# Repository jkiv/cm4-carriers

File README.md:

# cm4-carriers

## About

This repository contains various Raspberry Pi Compute Module 4 (CM4) carrier boards designed with specific applications in mind.

It also contains "template" boards from which application-specific boards can be quickly derived.

## Boards

### `hardware/cm4-carrier-template`

#### About
A 90mm x 90mm carrier board that can be used as a basis for application-specific boards.

This board can also be used to program the eMMC memory for use on other carrier boards.

#### Features
* Independent power and data USB 2.0 connectors (Type-C)

### `hardware/cm4-carrier-net`

#### About
A 40mm x 90mm carrier board that provides the CM4 with a Gigabit Ethernet interface.

This board can also be used to program the eMMC memory for use on other carrier boards.

#### Features
* Gigabit Ethernet
* USB 2.0 shared power and data connector (Type-C)
* Micro SD card slot

## Donate

Please consider supporting this project and others like it by donating:

* ☕: [ko-fi.com/jkiv_](https://ko-fi.com/jkiv_)
* ₿: `13zRrs1YDdooUN5WtfXRSDn8KnJdok4qG9`

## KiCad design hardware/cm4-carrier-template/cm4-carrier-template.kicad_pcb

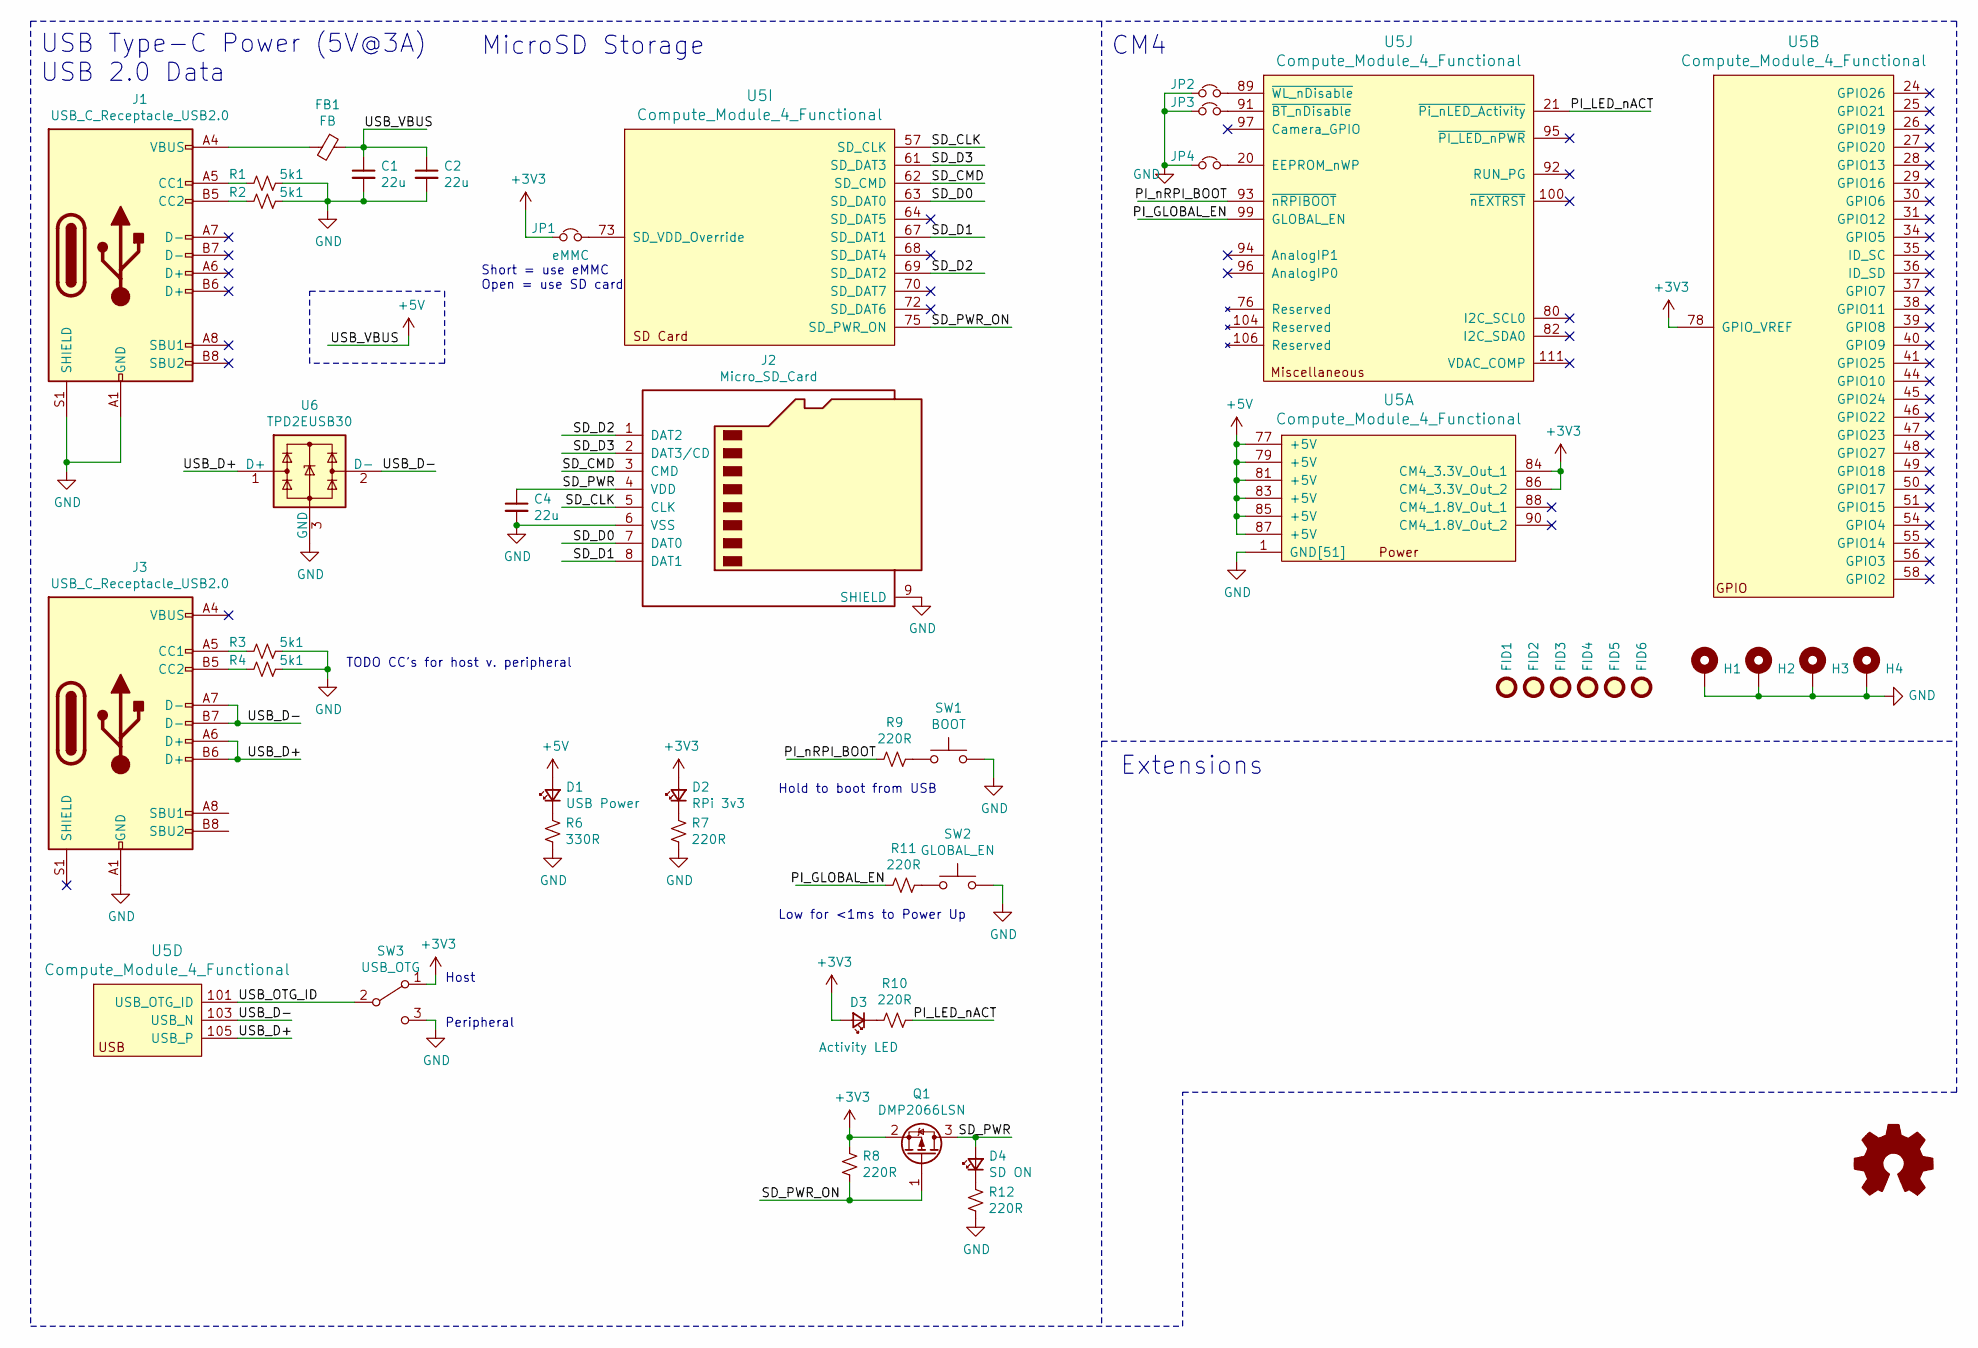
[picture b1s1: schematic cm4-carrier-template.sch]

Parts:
C1, C2, C4: 22u; C_0805_2012Metric
D1: USB Power; LED_0603_1608Metric
D2: RPi 3v3; LED_0603_1608Metric
D3: Activity LED; LED_0603_1608Metric
D4: SD ON; LED_0603_1608Metric
FB1: FB; L_0805_2012Metric
FID1, FID2, FID3, FID4, FID5, FID6: Fiducial; Fiducial_0.75mm_Mask1.5mm
H1, H2, H3, H4: MountingHole_Pad; MountingHole_2.7mm_M2.5_Pad_Via
J1, J3: USB_C_Receptacle_USB2.0; USB_C_Receptacle_GCT-USB4105
J2: Micro_SD_Card; microSD_HC_Molex_104031-0811
JP1: eMMC; J_Small_NC
JP2: ~WL_nDisable; J_Small_NC
JP3: ~BT_nDisable; J_Small_NC
JP4: EEPROM_nWP; J_Small_NC
LOGO1: Logo_Open_Hardware_Small; OSHW-Symbol_6.7x6mm_Copper
Q1: DMP2066LSN; SC-59
R1, R2, R3, R4: 5k1; R_0603_1608Metric
R6: 330R; R_0603_1608Metric
R7, R8, R9, R10, R11, R12: 220R; R_0603_1608Metric
SW1: BOOT; SW_SPST_B3U-1000P
SW2: GLOBAL_EN; SW_SPST_B3U-1000P
SW3: USB_OTG; SW_SPDT_CK-JS102011SAQN
U5: Compute_Module_4_Functional; Raspberry-Pi-4-Compute-Module
U6: TPD2EUSB30; Texas_DRT-3

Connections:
+3V3: D2.2 (A), D3.2 (A), JP1.1, Q1.2 (S), R8.2, SW3.1 (A), U5.78 (GPIO_VREF), U5.84 (CM4_3.3V_Out_1), U5.86 (CM4_3.3V_Out_2)
+5V: C1.1, C2.1, D1.2 (A), FB1.1, U5.77 (+5V), U5.79 (+5V), U5.81 (+5V), U5.83 (+5V), U5.85 (+5V), U5.87 (+5V)
/PI_GLOBAL_EN: R11.2, U5.99 (GLOBAL_EN)
/PI_LED_nACT: R10.1, U5.21 (~Pi_nLED_Activity)
/PI_nRPI_BOOT: R9.2, U5.93 (~nRPIBOOT)
/SD_CLK: J2.5 (CLK), U5.57 (SD_CLK)
/SD_CMD: J2.3 (CMD), U5.62 (SD_CMD)
/SD_D0: J2.7 (DAT0), U5.63 (SD_DAT0)
/SD_D1: J2.8 (DAT1), U5.67 (SD_DAT1)
/SD_D2: J2.1 (DAT2), U5.69 (SD_DAT2)
/SD_D3: J2.2 (DAT3/CD), U5.61 (SD_DAT3)
/SD_PWR: C4.1, D4.2 (A), J2.4 (VDD), Q1.3 (D)
/SD_PWR_ON: Q1.1 (G), R8.1, U5.75 (SD_PWR_ON)
/USB_D+: J3.A6 (D+), J3.B6 (D+), U5.105 (USB_P), U6.1 (D+)
/USB_D-: J3.A7 (D-), J3.B7 (D-), U5.103 (USB_N), U6.2 (D-)
/USB_OTG_ID: SW3.2 (B), U5.101 (USB_OTG_ID)
GND: C1.2, C2.2, C4.2, H1.1, H2.1, H3.1, H4.1, J1.A1 (GND), J1.A12 (GND), J1.B1 (GND), J1.B12 (GND), J1.S1 (SHIELD), J2.6 (VSS), J2.9 (SHIELD), J3.A1 (GND), J3.A12 (GND), J3.B1 (GND), J3.B12 (GND), JP2.1, JP3.1, JP4.1, R1.1, R2.1, R3.1, R4.1, R6.2, R7.2, R12.2, SW1.2, SW2.2, SW3.3 (C), U5.1 (GND[51]), U5.2 (GND[51]), U5.7 (GND[51]), U5.8 (GND[51]), U5.13 (GND[51]), U5.14 (GND[51]), U5.22 (GND[51]), U5.23 (GND[51]), U5.32 (GND[51]), U5.33 (GND[51]), U5.42 (GND[51]), U5.43 (GND[51]), U5.52 (GND[51]), U5.53 (GND[51]), U5.59 (GND[51]), U5.60 (GND[51]), U5.65 (GND[51]), U5.66 (GND[51]), U5.71 (GND[51]), U5.74 (GND[51]), U5.98 (GND[51]), U5.107 (GND[51]), U5.108 (GND[51]), U5.113 (GND[51]), U5.114 (GND[51]), U5.119 (GND[51]), U5.120 (GND[51]), U5.125 (GND[51]), U5.126 (GND[51]), U5.131 (GND[51]), U5.132 (GND[51]), U5.137 (GND[51]), U5.138 (GND[51]), U5.144 (GND[51]), U5.150 (GND[51]), U5.155 (GND[51]), U5.156 (GND[51]), U5.161 (GND[51]), U5.162 (GND[51]), U5.167 (GND[51]), U5.168 (GND[51]), U5.173 (GND[51]), U5.174 (GND[51]), U5.179 (GND[51]), U5.180 (GND[51]), U5.185 (GND[51]), U5.186 (GND[51]), U5.191 (GND[51]), U5.192 (GND[51]), U5.197 (GND[51]), U5.198 (GND[51]), U6.3 (GND)
unnamed: D1.1 (K), R6.1
unnamed: D2.1 (K), R7.1
unnamed: D3.1 (K), R10.2
unnamed: D4.1 (K), R12.1
unnamed: FB1.2, J1.A4 (VBUS), J1.A9 (VBUS), J1.B4 (VBUS), J1.B9 (VBUS)
unnamed: J1.A5 (CC1), R1.2
unnamed: J1.B5 (CC2), R2.2
unnamed: J3.A4 (VBUS), J3.A9 (VBUS), J3.B4 (VBUS), J3.B9 (VBUS)
unnamed: J3.A5 (CC1), R3.2
unnamed: J3.B5 (CC2), R4.2
unnamed: JP1.2, U5.73 (SD_VDD_Override)
unnamed: JP2.2, U5.89 (~WL_nDisable)
unnamed: JP3.2, U5.91 (~BT_nDisable)
unnamed: JP4.2, U5.20 (EEPROM_nWP)
unnamed: R9.1, SW1.1
unnamed: R11.1, SW2.1

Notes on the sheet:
USB Type-C Power (5V@3A) USB 2.0 Data
MicroSD Storage
CM4
Extensions
Low for <1ms to Power Up
Short = use eMMC Open = use SD card
Hold to boot from USB
Host
Peripheral
TODO CC's for host v. peripheral

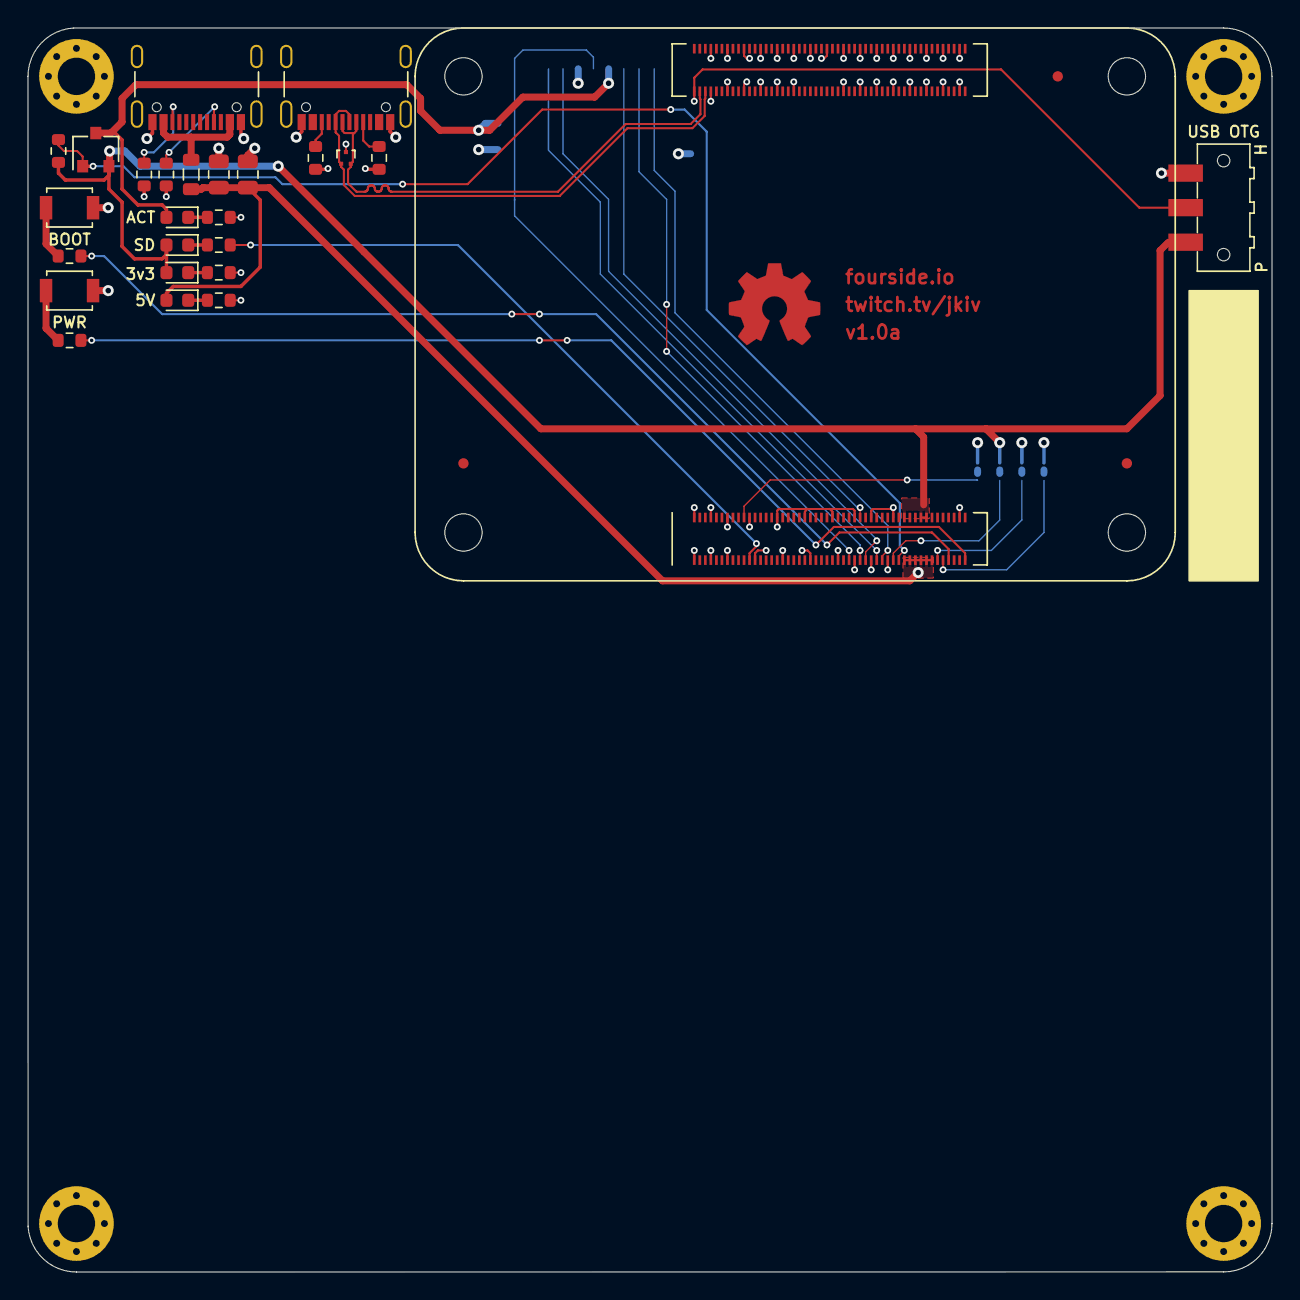
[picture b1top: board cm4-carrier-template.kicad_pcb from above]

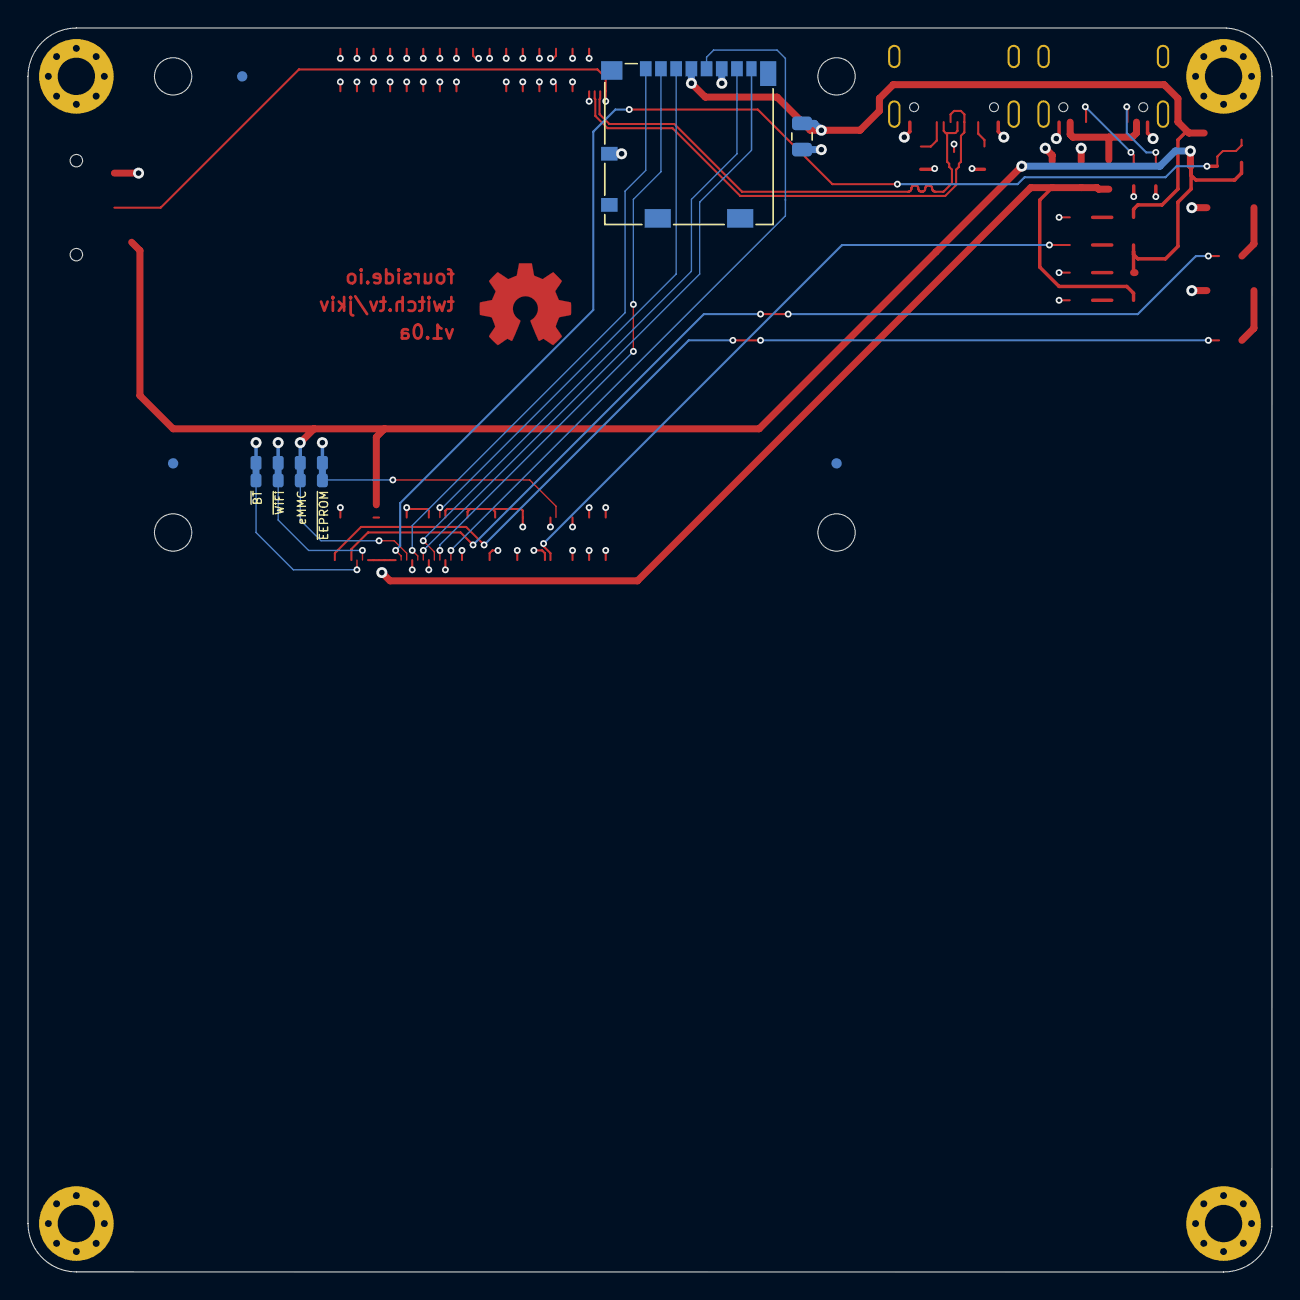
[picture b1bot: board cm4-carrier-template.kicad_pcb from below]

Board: 4 copper layers, 90.0 x 90.0 mm, 43 parts (9 on the bottom side), 33 nets.

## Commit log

2021-09-07 Added submodule dependencies.
2021-09-07 jkiv-kicad-library tracking dev branch.
2021-09-08 Basic CM4 board template -- 90mm x 90mm -- with PoE extension.
2021-09-08 Forgot to commit PCB.
2021-09-08 Added README.md
2021-09-08 Cleaned up project imports.
2021-09-12 Post-stream commit.
2021-09-17 Pre-stream commit.
2021-09-17 Finished layout for 40mmx90mm base carrier.
2021-09-17 Tracking up-to-date jkiv-kicad-library
2021-09-17 Updated wording in README.
2021-09-17 Small adjustment to signal paths to make space on backside.
2021-09-17 Fixed disconnected 'SD enabled' LED.
2021-09-17 Removed references to extra symbol libraries.
2021-09-17 Removed digi-key from submodules.
2021-09-17 Ok. Symbol libraries /should/ be fixed... 🤞
2021-09-17 Updated USB connector to what is available. Generated gerbers, HTMLBOM.
2021-09-17 Renaming 40mmx90mm gigabit Ethernet board to cm4-carrier-net.
2021-09-17 Updated metadata for cm4-carrier-net PCB.
2021-09-17 Added 90mm x 90mm 'template' schematic and PCB.
2021-09-18 Added USB OTG ID selection switch. Likely finalized v1.0a.
2021-09-24 Reworked cm4-carrier-template using latest cm4-carrier-net as base.
